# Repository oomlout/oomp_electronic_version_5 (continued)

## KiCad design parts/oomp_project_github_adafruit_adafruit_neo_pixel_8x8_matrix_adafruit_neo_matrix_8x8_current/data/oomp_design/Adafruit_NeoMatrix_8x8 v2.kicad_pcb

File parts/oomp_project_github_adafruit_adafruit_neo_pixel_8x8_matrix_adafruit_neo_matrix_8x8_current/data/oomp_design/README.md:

# OOMP KiCad design copy

Open `Adafruit_NeoMatrix_8x8 v2.kicad_pro` (or the `.kicad_pcb` / `.kicad_sch`) in KiCad. Local OOMP libraries are under `libraries/`. Original inputs are preserved in [../original/](../original/).

Only verified unchanged installed KiCad defaults were renamed. Modified, custom, unmatched and unavailable items remain unchanged. Soldering variants are never swapped during conversion. Existing pad coordinates, nets and UUIDs are preserved.

See [conversion_report.yaml](conversion_report.yaml) for every conversion and skip. Copy this directory before editing; regeneration refuses to overwrite edited design files.

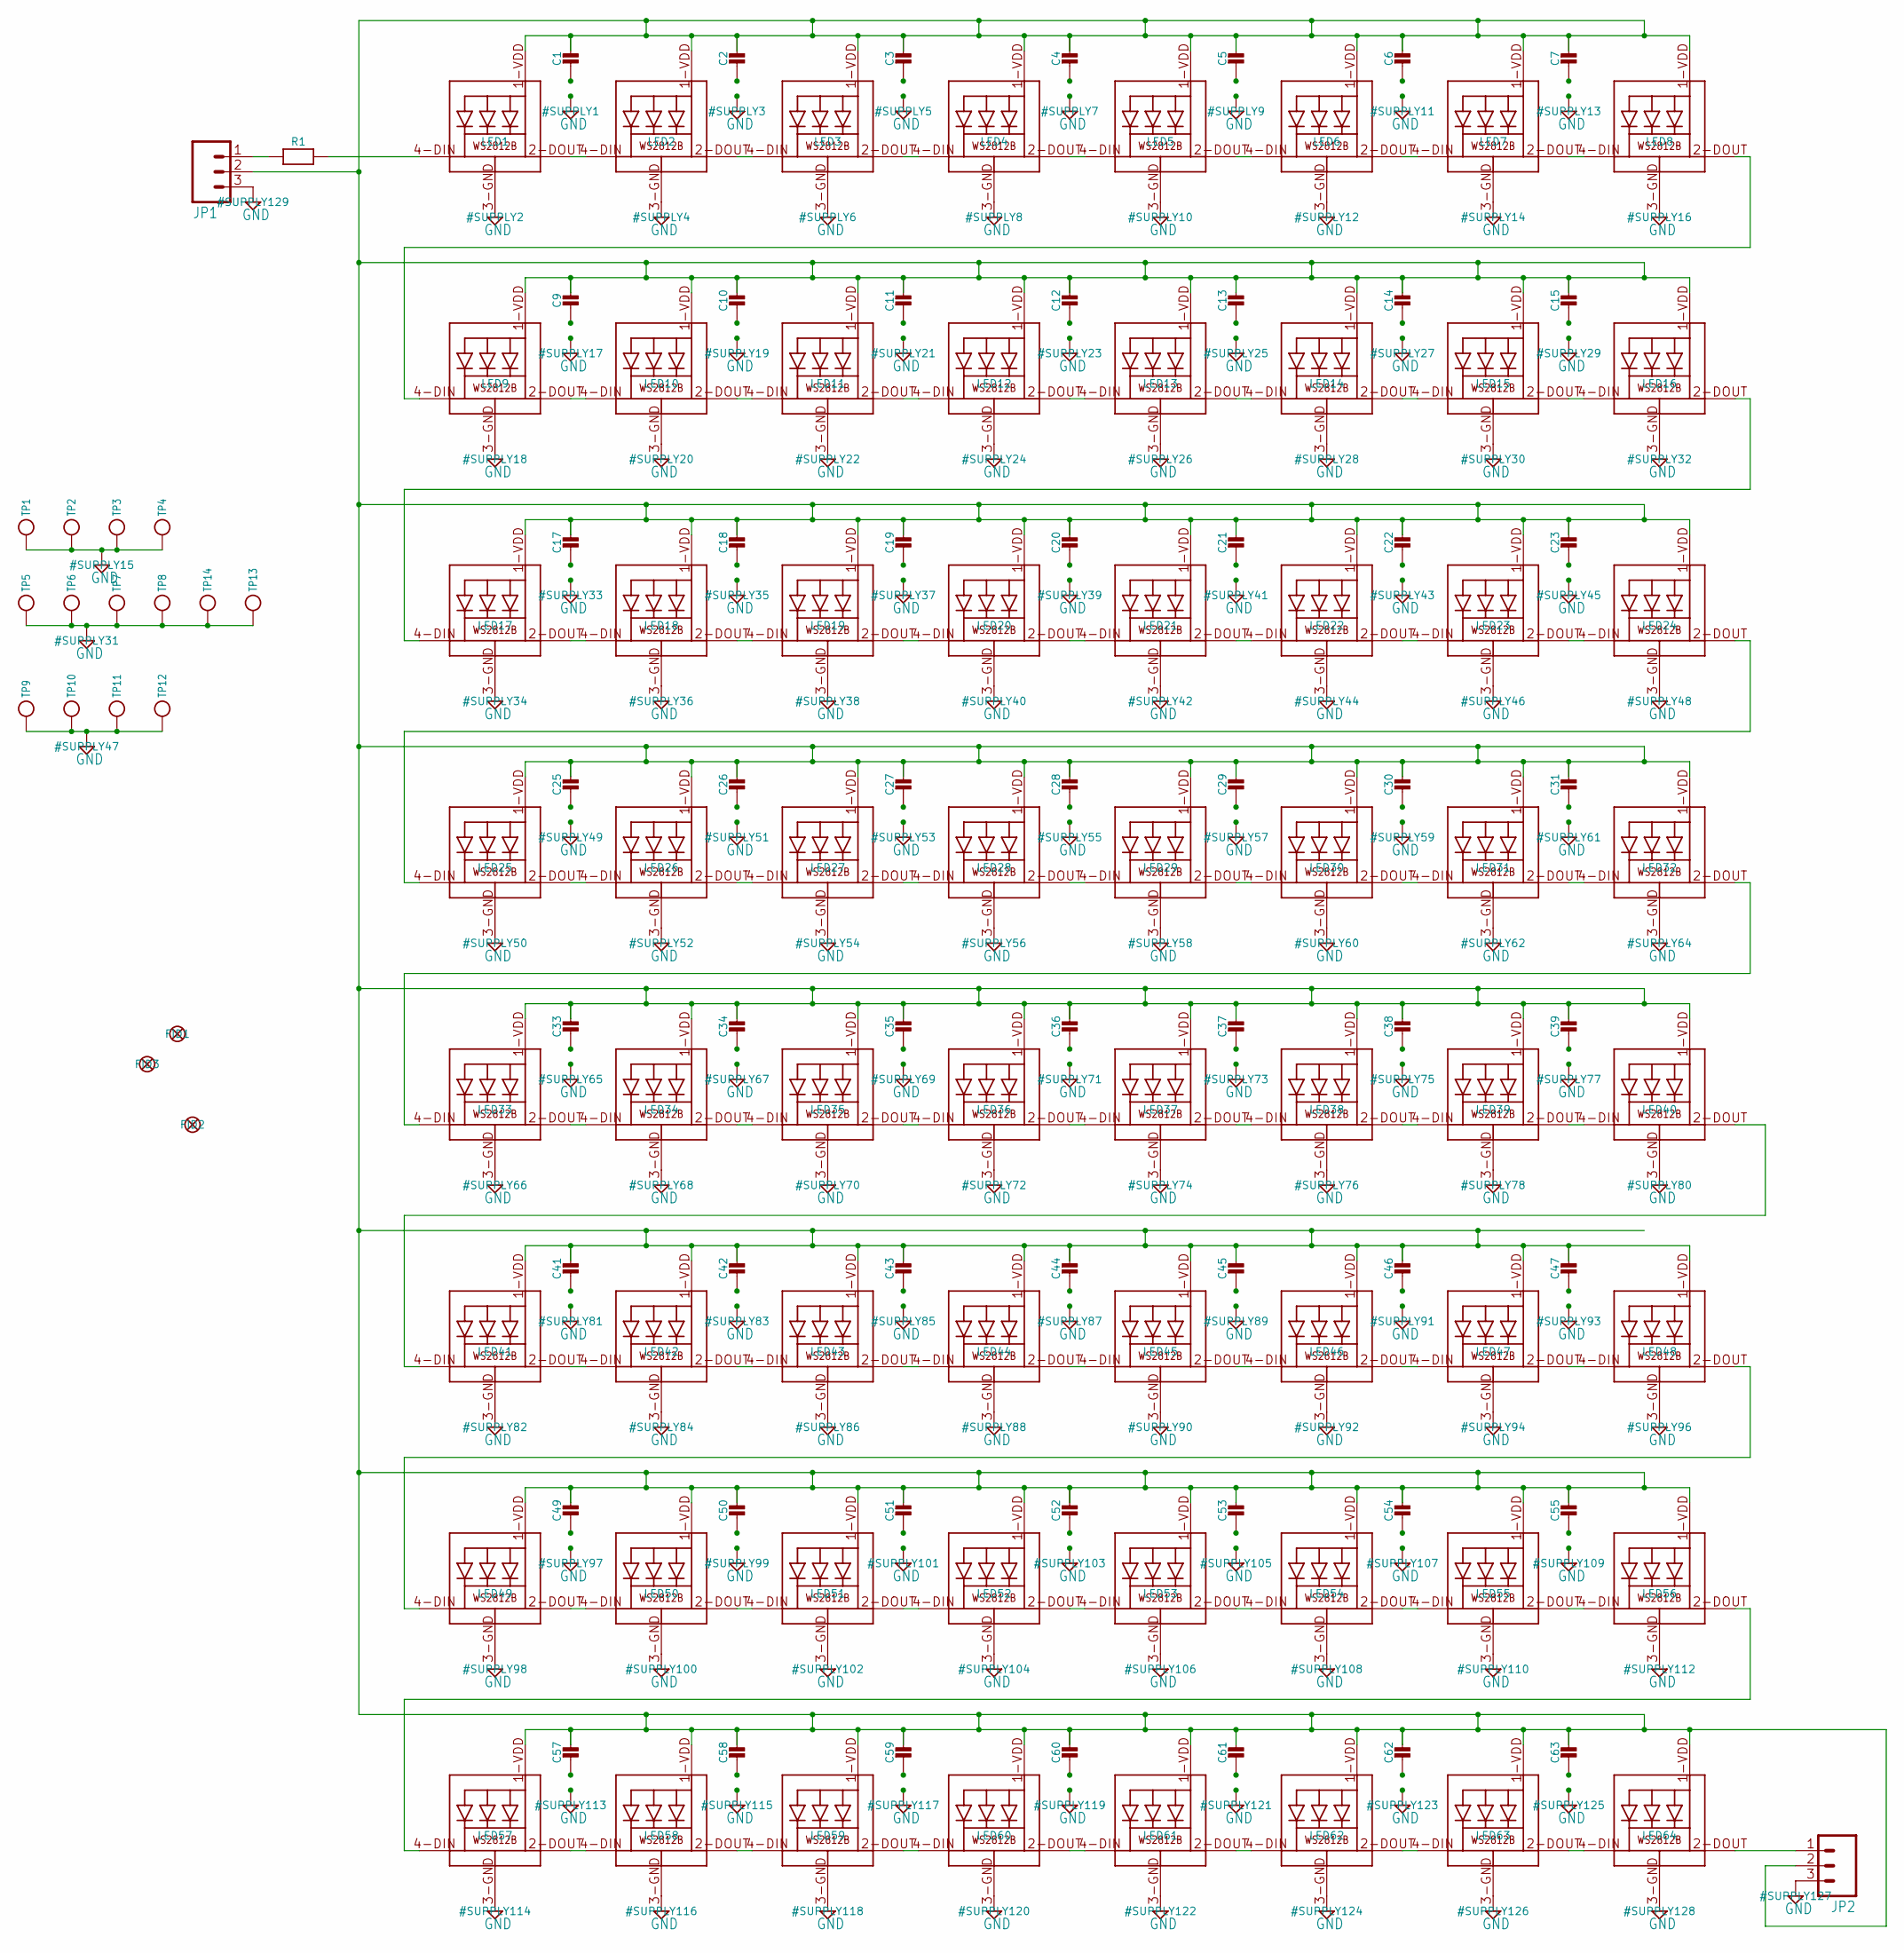
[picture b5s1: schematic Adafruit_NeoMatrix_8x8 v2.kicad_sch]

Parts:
C1, C2, C3, C4, C5, C6, C7, C9, C10, C11, C12, C13, C14, C15, C17, C18, C19, C20, C21, C22, C23, C25, C26, C27, C28, C29, C30, C31, C33, C34, C35, C36, C37, C38, C39, C41, C42, C43, C44, C45, C46, C47, C49, C50, C51, C52, C53, C54, C55, C57, C58, C59, C60, C61, C62, C63: CAP_CERAMIC0805-NOOUTLINE; 0805-NO
FID1, FID2, FID3: FIDUCIAL""; FIDUCIAL_1MM
JP1, JP2: M03PTH; 1X03
LED1, LED2, LED3, LED4, LED5, LED6, LED7, LED8, LED9, LED10, LED11, LED12, LED13, LED14, LED15, LED16, LED17, LED18, LED19, LED20, LED21, LED22, LED23, LED24, LED25, LED26, LED27, LED28, LED29, LED30, LED31, LED32, LED33, LED34, LED35, LED36, LED37, LED38, LED39, LED40, LED41, LED42, LED43, LED44, LED45, LED46, LED47, LED48, LED49, LED50, LED51, LED52, LED53, LED54, LED55, LED56, LED57, LED58, LED59, LED60, LED61, LED62, LED63, LED64: WS2812B5050; WS2812B
R1: RESISTOR0805_NOOUTLINE; 0805-NO
TP1, TP2, TP3, TP4, TP5, TP6, TP7, TP8, TP9, TP10, TP11, TP12, TP13, TP14: TESTPOINT; TESTPOINT_SMT

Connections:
GND: C1.2, C2.2, C3.2, C4.2, C5.2, C6.2, C7.2, C9.2, C10.2, C11.2, C12.2, C13.2, C14.2, C15.2, C17.2, C18.2, C19.2, C20.2, C21.2, C22.2, C23.2, C25.2, C26.2, C27.2, C28.2, C29.2, C30.2, C31.2, C33.2, C34.2, C35.2, C36.2, C37.2, C38.2, C39.2, C41.2, C42.2, C43.2, C44.2, C45.2, C46.2, C47.2, C49.2, C50.2, C51.2, C52.2, C53.2, C54.2, C55.2, C57.2, C58.2, C59.2, C60.2, C61.2, C62.2, C63.2, JP1.3, JP2.3, LED1.3-GND (GND), LED2.3-GND (GND), LED3.3-GND (GND), LED4.3-GND (GND), LED5.3-GND (GND), LED6.3-GND (GND), LED7.3-GND (GND), LED8.3-GND (GND), LED9.3-GND (GND), LED10.3-GND (GND), LED11.3-GND (GND), LED12.3-GND (GND), LED13.3-GND (GND), LED14.3-GND (GND), LED15.3-GND (GND), LED16.3-GND (GND), LED17.3-GND (GND), LED18.3-GND (GND), LED19.3-GND (GND), LED20.3-GND (GND), LED21.3-GND (GND), LED22.3-GND (GND), LED23.3-GND (GND), LED24.3-GND (GND), LED25.3-GND (GND), LED26.3-GND (GND), LED27.3-GND (GND), LED28.3-GND (GND), LED29.3-GND (GND), LED30.3-GND (GND), LED31.3-GND (GND), LED32.3-GND (GND), LED33.3-GND (GND), LED34.3-GND (GND), LED35.3-GND (GND), LED36.3-GND (GND), LED37.3-GND (GND), LED38.3-GND (GND), LED39.3-GND (GND), LED40.3-GND (GND), LED41.3-GND (GND), LED42.3-GND (GND), LED43.3-GND (GND), LED44.3-GND (GND), LED45.3-GND (GND), LED46.3-GND (GND), LED47.3-GND (GND), LED48.3-GND (GND), LED49.3-GND (GND), LED50.3-GND (GND), LED51.3-GND (GND), LED52.3-GND (GND), LED53.3-GND (GND), LED54.3-GND (GND), LED55.3-GND (GND), LED56.3-GND (GND), LED57.3-GND (GND), LED58.3-GND (GND), LED59.3-GND (GND), LED60.3-GND (GND), LED61.3-GND (GND), LED62.3-GND (GND), LED63.3-GND (GND), LED64.3-GND (GND), TP1.P$1, TP2.P$1, TP3.P$1, TP4.P$1, TP5.P$1, TP6.P$1, TP7.P$1, TP8.P$1, TP9.P$1, TP10.P$1, TP11.P$1, TP12.P$1, TP13.P$1, TP14.P$1
unnamed: LED1.4-DIN (DI), R1.2
unnamed: LED8.2-DOUT (DO), LED9.4-DIN (DI)
unnamed: LED16.2-DOUT (DO), LED17.4-DIN (DI)
unnamed: LED24.2-DOUT (DO), LED25.4-DIN (DI)
unnamed: LED40.2-DOUT (DO), LED41.4-DIN (DI)
unnamed: LED32.2-DOUT (DO), LED33.4-DIN (DI)
unnamed: LED48.2-DOUT (DO), LED49.4-DIN (DI)
unnamed: LED56.2-DOUT (DO), LED57.4-DIN (DI)
unnamed: JP2.1, LED64.2-DOUT (DO)
unnamed: JP1.1, R1.1
unnamed: LED17.2-DOUT (DO), LED18.4-DIN (DI)
unnamed: LED25.2-DOUT (DO), LED26.4-DIN (DI)
unnamed: LED26.2-DOUT (DO), LED27.4-DIN (DI)
unnamed: LED2.2-DOUT (DO), LED3.4-DIN (DI)
unnamed: LED3.2-DOUT (DO), LED4.4-DIN (DI)
unnamed: LED4.2-DOUT (DO), LED5.4-DIN (DI)
unnamed: LED5.2-DOUT (DO), LED6.4-DIN (DI)
unnamed: LED6.2-DOUT (DO), LED7.4-DIN (DI)
unnamed: LED7.2-DOUT (DO), LED8.4-DIN (DI)
unnamed: LED10.2-DOUT (DO), LED11.4-DIN (DI)
unnamed: LED11.2-DOUT (DO), LED12.4-DIN (DI)
unnamed: LED12.2-DOUT (DO), LED13.4-DIN (DI)
unnamed: LED13.2-DOUT (DO), LED14.4-DIN (DI)
unnamed: LED14.2-DOUT (DO), LED15.4-DIN (DI)
unnamed: LED15.2-DOUT (DO), LED16.4-DIN (DI)
unnamed: LED18.2-DOUT (DO), LED19.4-DIN (DI)
unnamed: LED19.2-DOUT (DO), LED20.4-DIN (DI)
unnamed: LED20.2-DOUT (DO), LED21.4-DIN (DI)
unnamed: LED21.2-DOUT (DO), LED22.4-DIN (DI)
unnamed: LED22.2-DOUT (DO), LED23.4-DIN (DI)
unnamed: LED23.2-DOUT (DO), LED24.4-DIN (DI)
unnamed: LED27.2-DOUT (DO), LED28.4-DIN (DI)
unnamed: LED28.2-DOUT (DO), LED29.4-DIN (DI)
unnamed: LED29.2-DOUT (DO), LED30.4-DIN (DI)
unnamed: LED30.2-DOUT (DO), LED31.4-DIN (DI)
unnamed: LED31.2-DOUT (DO), LED32.4-DIN (DI)
unnamed: LED1.2-DOUT (DO), LED2.4-DIN (DI)
unnamed: LED9.2-DOUT (DO), LED10.4-DIN (DI)
unnamed: LED49.2-DOUT (DO), LED50.4-DIN (DI)
unnamed: LED57.2-DOUT (DO), LED58.4-DIN (DI)
unnamed: LED58.2-DOUT (DO), LED59.4-DIN (DI)
unnamed: LED34.2-DOUT (DO), LED35.4-DIN (DI)
unnamed: LED35.2-DOUT (DO), LED36.4-DIN (DI)
unnamed: LED36.2-DOUT (DO), LED37.4-DIN (DI)
unnamed: LED37.2-DOUT (DO), LED38.4-DIN (DI)
unnamed: LED38.2-DOUT (DO), LED39.4-DIN (DI)
unnamed: LED39.2-DOUT (DO), LED40.4-DIN (DI)
unnamed: LED42.2-DOUT (DO), LED43.4-DIN (DI)
unnamed: LED43.2-DOUT (DO), LED44.4-DIN (DI)
unnamed: LED44.2-DOUT (DO), LED45.4-DIN (DI)
unnamed: LED45.2-DOUT (DO), LED46.4-DIN (DI)
unnamed: LED46.2-DOUT (DO), LED47.4-DIN (DI)
unnamed: LED47.2-DOUT (DO), LED48.4-DIN (DI)
unnamed: LED50.2-DOUT (DO), LED51.4-DIN (DI)
unnamed: LED51.2-DOUT (DO), LED52.4-DIN (DI)
unnamed: LED52.2-DOUT (DO), LED53.4-DIN (DI)
unnamed: LED53.2-DOUT (DO), LED54.4-DIN (DI)
unnamed: LED54.2-DOUT (DO), LED55.4-DIN (DI)
unnamed: LED55.2-DOUT (DO), LED56.4-DIN (DI)
unnamed: LED59.2-DOUT (DO), LED60.4-DIN (DI)
unnamed: LED60.2-DOUT (DO), LED61.4-DIN (DI)
unnamed: LED61.2-DOUT (DO), LED62.4-DIN (DI)
unnamed: LED62.2-DOUT (DO), LED63.4-DIN (DI)
unnamed: LED63.2-DOUT (DO), LED64.4-DIN (DI)
unnamed: LED33.2-DOUT (DO), LED34.4-DIN (DI)
unnamed: LED41.2-DOUT (DO), LED42.4-DIN (DI)
VDD: C1.1, C2.1, C3.1, C4.1, C5.1, C6.1, C7.1, C9.1, C10.1, C11.1, C12.1, C13.1, C14.1, C15.1, C17.1, C18.1, C19.1, C20.1, C21.1, C22.1, C23.1, C25.1, C26.1, C27.1, C28.1, C29.1, C30.1, C31.1, C33.1, C34.1, C35.1, C36.1, C37.1, C38.1, C39.1, C41.1, C42.1, C43.1, C44.1, C45.1, C46.1, C47.1, C49.1, C50.1, C51.1, C52.1, C53.1, C54.1, C55.1, C57.1, C58.1, C59.1, C60.1, C61.1, C62.1, C63.1, JP1.2, JP2.2, LED1.1-VDD (VDD), LED2.1-VDD (VDD), LED3.1-VDD (VDD), LED4.1-VDD (VDD), LED5.1-VDD (VDD), LED6.1-VDD (VDD), LED7.1-VDD (VDD), LED8.1-VDD (VDD), LED9.1-VDD (VDD), LED10.1-VDD (VDD), LED11.1-VDD (VDD), LED12.1-VDD (VDD), LED13.1-VDD (VDD), LED14.1-VDD (VDD), LED15.1-VDD (VDD), LED16.1-VDD (VDD), LED17.1-VDD (VDD), LED18.1-VDD (VDD), LED19.1-VDD (VDD), LED20.1-VDD (VDD), LED21.1-VDD (VDD), LED22.1-VDD (VDD), LED23.1-VDD (VDD), LED24.1-VDD (VDD), LED25.1-VDD (VDD), LED26.1-VDD (VDD), LED27.1-VDD (VDD), LED28.1-VDD (VDD), LED29.1-VDD (VDD), LED30.1-VDD (VDD), LED31.1-VDD (VDD), LED32.1-VDD (VDD), LED33.1-VDD (VDD), LED34.1-VDD (VDD), LED35.1-VDD (VDD), LED36.1-VDD (VDD), LED37.1-VDD (VDD), LED38.1-VDD (VDD), LED39.1-VDD (VDD), LED40.1-VDD (VDD), LED41.1-VDD (VDD), LED42.1-VDD (VDD), LED43.1-VDD (VDD), LED44.1-VDD (VDD), LED45.1-VDD (VDD), LED46.1-VDD (VDD), LED47.1-VDD (VDD), LED48.1-VDD (VDD), LED49.1-VDD (VDD), LED50.1-VDD (VDD), LED51.1-VDD (VDD), LED52.1-VDD (VDD), LED53.1-VDD (VDD), LED54.1-VDD (VDD), LED55.1-VDD (VDD), LED56.1-VDD (VDD), LED57.1-VDD (VDD), LED58.1-VDD (VDD), LED59.1-VDD (VDD), LED60.1-VDD (VDD), LED61.1-VDD (VDD), LED62.1-VDD (VDD), LED63.1-VDD (VDD), LED64.1-VDD (VDD)

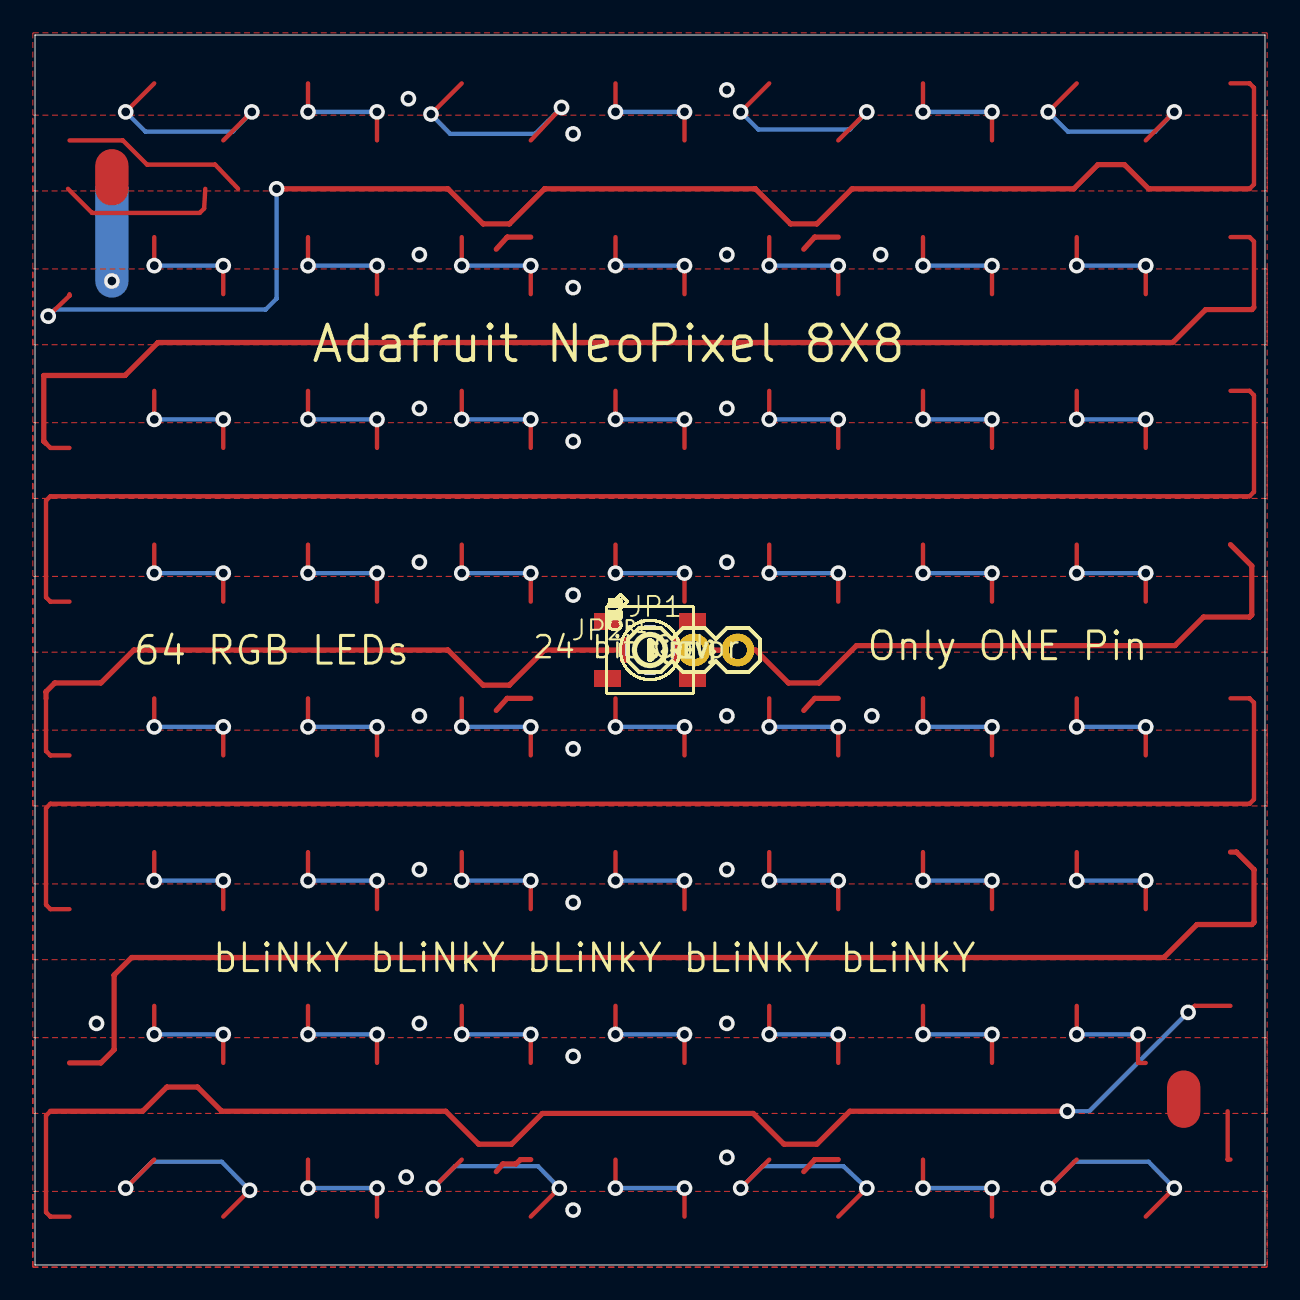
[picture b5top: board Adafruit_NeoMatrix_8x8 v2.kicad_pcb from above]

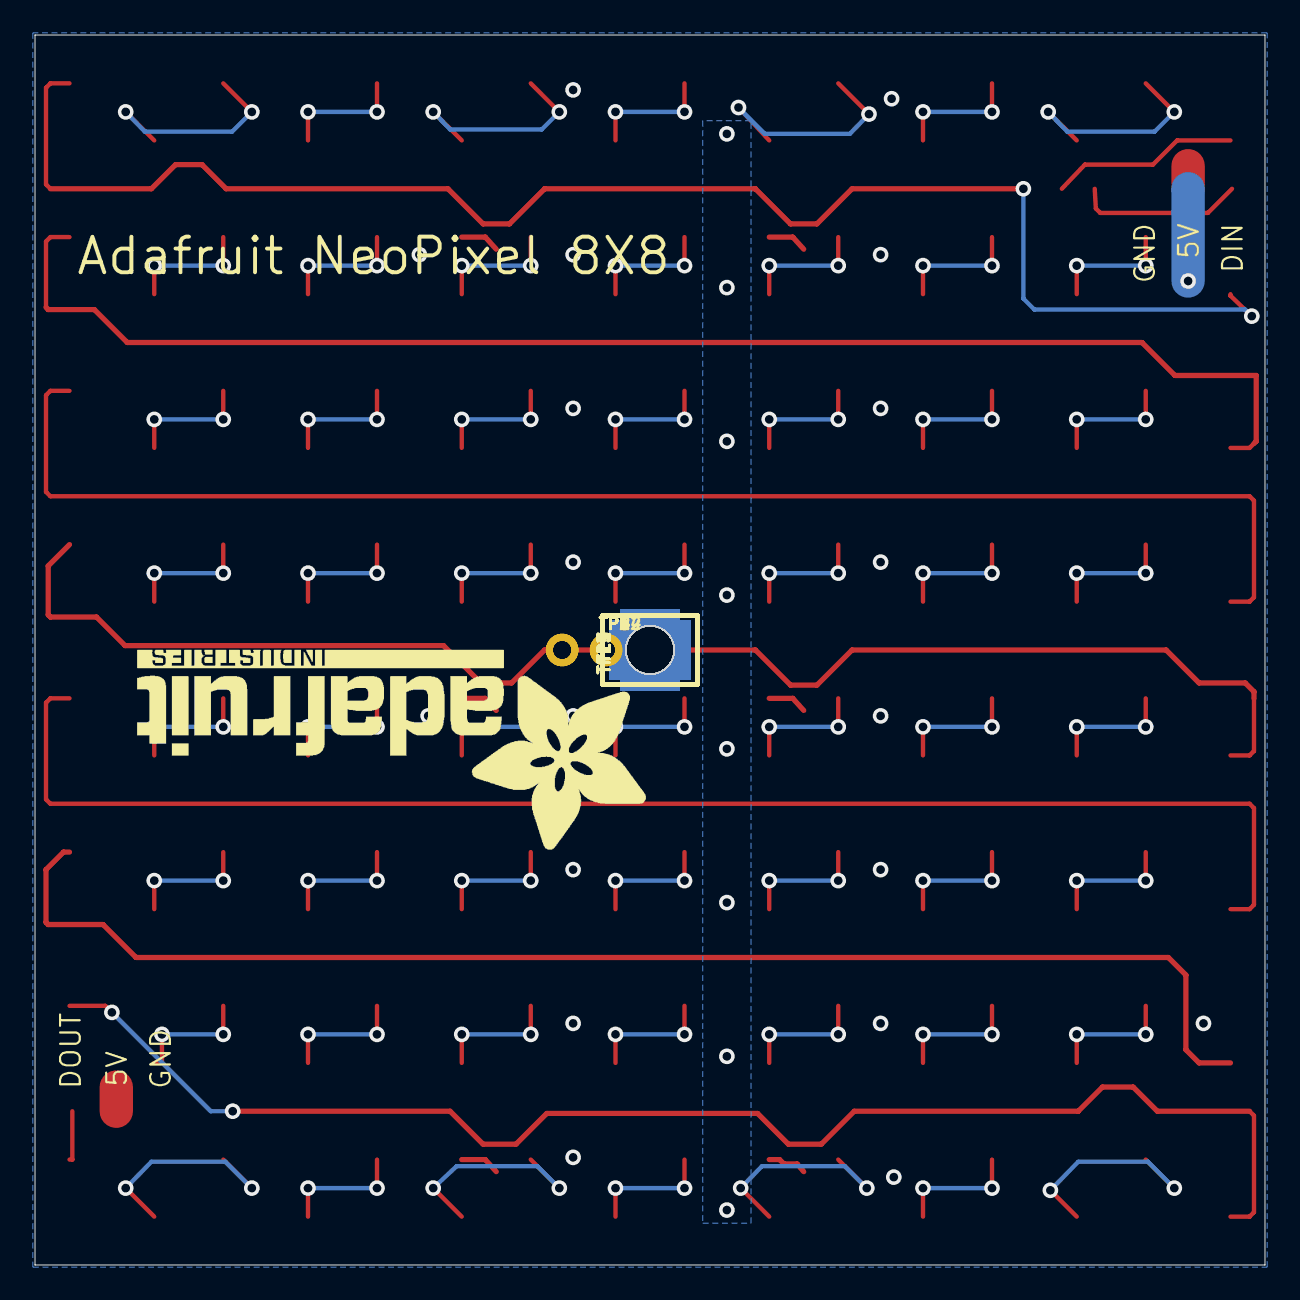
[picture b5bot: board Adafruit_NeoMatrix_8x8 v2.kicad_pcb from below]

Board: 2 copper layers, 71.1 x 71.1 mm, 154 parts (15 on the bottom side), 68 nets.

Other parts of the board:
U$1: ADAFRUIT_TEXT_30MM
U$2: PCBFEAT-REV-040
UNK_HOLE_0: dummyfp0
UNK_HOLE_1: dummyfp1
UNK_HOLE_2: dummyfp2
UNK_HOLE_3: dummyfp3
UNK_HOLE_4: dummyfp4
UNK_HOLE_5: dummyfp5
UNK_HOLE_6: dummyfp6
UNK_HOLE_7: dummyfp7
UNK_HOLE_8: dummyfp8
UNK_HOLE_9: dummyfp9
UNK_HOLE_10: dummyfp10
UNK_HOLE_11: dummyfp11

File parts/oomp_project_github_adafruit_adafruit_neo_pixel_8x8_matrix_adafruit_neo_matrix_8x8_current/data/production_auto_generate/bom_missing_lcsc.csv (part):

Designator,Comment,Footprint,OOMP ID,Reason
C1,,Adafruit_NeoMatrix_8x8 v2-import-fps:0805-NO,,No verified LCSC part number
C2,,Adafruit_NeoMatrix_8x8 v2-import-fps:0805-NO,,No verified LCSC part number
C3,,Adafruit_NeoMatrix_8x8 v2-import-fps:0805-NO,,No verified LCSC part number
C4,,Adafruit_NeoMatrix_8x8 v2-import-fps:0805-NO,,No verified LCSC part number
C5,,Adafruit_NeoMatrix_8x8 v2-import-fps:0805-NO,,No verified LCSC part number
C6,,Adafruit_NeoMatrix_8x8 v2-import-fps:0805-NO,,No verified LCSC part number
C7,,Adafruit_NeoMatrix_8x8 v2-import-fps:0805-NO,,No verified LCSC part number
C9,,Adafruit_NeoMatrix_8x8 v2-import-fps:0805-NO,,No verified LCSC part number
C10,,Adafruit_NeoMatrix_8x8 v2-import-fps:0805-NO,,No verified LCSC part number
C11,,Adafruit_NeoMatrix_8x8 v2-import-fps:0805-NO,,No verified LCSC part number
C12,,Adafruit_NeoMatrix_8x8 v2-import-fps:0805-NO,,No verified LCSC part number
C13,,Adafruit_NeoMatrix_8x8 v2-import-fps:0805-NO,,No verified LCSC part number
C14,,Adafruit_NeoMatrix_8x8 v2-import-fps:0805-NO,,No verified LCSC part number
C15,,Adafruit_NeoMatrix_8x8 v2-import-fps:0805-NO,,No verified LCSC part number
C17,,Adafruit_NeoMatrix_8x8 v2-import-fps:0805-NO,,No verified LCSC part number
C18,,Adafruit_NeoMatrix_8x8 v2-import-fps:0805-NO,,No verified LCSC part number
C19,,Adafruit_NeoMatrix_8x8 v2-import-fps:0805-NO,,No verified LCSC part number
C20,,Adafruit_NeoMatrix_8x8 v2-import-fps:0805-NO,,No verified LCSC part number
C21,,Adafruit_NeoMatrix_8x8 v2-import-fps:0805-NO,,No verified LCSC part number
C22,,Adafruit_NeoMatrix_8x8 v2-import-fps:0805-NO,,No verified LCSC part number
C23,,Adafruit_NeoMatrix_8x8 v2-import-fps:0805-NO,,No verified LCSC part number
C25,,Adafruit_NeoMatrix_8x8 v2-import-fps:0805-NO,,No verified LCSC part number
C26,,Adafruit_NeoMatrix_8x8 v2-import-fps:0805-NO,,No verified LCSC part number
C27,,Adafruit_NeoMatrix_8x8 v2-import-fps:0805-NO,,No verified LCSC part number
C28,,Adafruit_NeoMatrix_8x8 v2-import-fps:0805-NO,,No verified LCSC part number
C29,,Adafruit_NeoMatrix_8x8 v2-import-fps:0805-NO,,No verified LCSC part number
C30,,Adafruit_NeoMatrix_8x8 v2-import-fps:0805-NO,,No verified LCSC part number
C31,,Adafruit_NeoMatrix_8x8 v2-import-fps:0805-NO,,No verified LCSC part number
C33,,Adafruit_NeoMatrix_8x8 v2-import-fps:0805-NO,,No verified LCSC part number
C34,,Adafruit_NeoMatrix_8x8 v2-import-fps:0805-NO,,No verified LCSC part number
C35,,Adafruit_NeoMatrix_8x8 v2-import-fps:0805-NO,,No verified LCSC part number
C36,,Adafruit_NeoMatrix_8x8 v2-import-fps:0805-NO,,No verified LCSC part number
C37,,Adafruit_NeoMatrix_8x8 v2-import-fps:0805-NO,,No verified LCSC part number
C38,,Adafruit_NeoMatrix_8x8 v2-import-fps:0805-NO,,No verified LCSC part number
C39,,Adafruit_NeoMatrix_8x8 v2-import-fps:0805-NO,,No verified LCSC part number
C41,,Adafruit_NeoMatrix_8x8 v2-import-fps:0805-NO,,No verified LCSC part number
C42,,Adafruit_NeoMatrix_8x8 v2-import-fps:0805-NO,,No verified LCSC part number
C43,,Adafruit_NeoMatrix_8x8 v2-import-fps:0805-NO,,No verified LCSC part number
C44,,Adafruit_NeoMatrix_8x8 v2-import-fps:0805-NO,,No verified LCSC part number
C45,,Adafruit_NeoMatrix_8x8 v2-import-fps:0805-NO,,No verified LCSC part number
C46,,Adafruit_NeoMatrix_8x8 v2-import-fps:0805-NO,,No verified LCSC part number
C47,,Adafruit_NeoMatrix_8x8 v2-import-fps:0805-NO,,No verified LCSC part number
C49,,Adafruit_NeoMatrix_8x8 v2-import-fps:0805-NO,,No verified LCSC part number
C50,,Adafruit_NeoMatrix_8x8 v2-import-fps:0805-NO,,No verified LCSC part number
C51,,Adafruit_NeoMatrix_8x8 v2-import-fps:0805-NO,,No verified LCSC part number
C52,,Adafruit_NeoMatrix_8x8 v2-import-fps:0805-NO,,No verified LCSC part number
C53,,Adafruit_NeoMatrix_8x8 v2-import-fps:0805-NO,,No verified LCSC part number
C54,,Adafruit_NeoMatrix_8x8 v2-import-fps:0805-NO,,No verified LCSC part number
C55,,Adafruit_NeoMatrix_8x8 v2-import-fps:0805-NO,,No verified LCSC part number
C57,,Adafruit_NeoMatrix_8x8 v2-import-fps:0805-NO,,No verified LCSC part number
C58,,Adafruit_NeoMatrix_8x8 v2-import-fps:0805-NO,,No verified LCSC part number
C59,,Adafruit_NeoMatrix_8x8 v2-import-fps:0805-NO,,No verified LCSC part number
C60,,Adafruit_NeoMatrix_8x8 v2-import-fps:0805-NO,,No verified LCSC part number
C61,,Adafruit_NeoMatrix_8x8 v2-import-fps:0805-NO,,No verified LCSC part number
C62,,Adafruit_NeoMatrix_8x8 v2-import-fps:0805-NO,,No verified LCSC part number
C63,,Adafruit_NeoMatrix_8x8 v2-import-fps:0805-NO,,No verified LCSC part number
LED1,WS2812B5050,Adafruit_NeoMatrix_8x8 v2-import-fps:WS2812B,electronic_led_5050_rgb_ws2812b_worldsemi_ws2812b_b_w,No verified LCSC part number
LED2,WS2812B5050,Adafruit_NeoMatrix_8x8 v2-import-fps:WS2812B,electronic_led_5050_rgb_ws2812b_worldsemi_ws2812b_b_w,No verified LCSC part number
LED3,WS2812B5050,Adafruit_NeoMatrix_8x8 v2-import-fps:WS2812B,electronic_led_5050_rgb_ws2812b_worldsemi_ws2812b_b_w,No verified LCSC part number
LED4,WS2812B5050,Adafruit_NeoMatrix_8x8 v2-import-fps:WS2812B,electronic_led_5050_rgb_ws2812b_worldsemi_ws2812b_b_w,No verified LCSC part number
LED5,WS2812B5050,Adafruit_NeoMatrix_8x8 v2-import-fps:WS2812B,electronic_led_5050_rgb_ws2812b_worldsemi_ws2812b_b_w,No verified LCSC part number
LED6,WS2812B5050,Adafruit_NeoMatrix_8x8 v2-import-fps:WS2812B,electronic_led_5050_rgb_ws2812b_worldsemi_ws2812b_b_w,No verified LCSC part number
LED7,WS2812B5050,Adafruit_NeoMatrix_8x8 v2-import-fps:WS2812B,electronic_led_5050_rgb_ws2812b_worldsemi_ws2812b_b_w,No verified LCSC part number
LED8,WS2812B5050,Adafruit_NeoMatrix_8x8 v2-import-fps:WS2812B,electronic_led_5050_rgb_ws2812b_worldsemi_ws2812b_b_w,No verified LCSC part number
LED9,WS2812B5050,Adafruit_NeoMatrix_8x8 v2-import-fps:WS2812B,electronic_led_5050_rgb_ws2812b_worldsemi_ws2812b_b_w,No verified LCSC part number
LED10,WS2812B5050,Adafruit_NeoMatrix_8x8 v2-import-fps:WS2812B,electronic_led_5050_rgb_ws2812b_worldsemi_ws2812b_b_w,No verified LCSC part number
LED11,WS2812B5050,Adafruit_NeoMatrix_8x8 v2-import-fps:WS2812B,electronic_led_5050_rgb_ws2812b_worldsemi_ws2812b_b_w,No verified LCSC part number
LED12,WS2812B5050,Adafruit_NeoMatrix_8x8 v2-import-fps:WS2812B,electronic_led_5050_rgb_ws2812b_worldsemi_ws2812b_b_w,No verified LCSC part number
LED13,WS2812B5050,Adafruit_NeoMatrix_8x8 v2-import-fps:WS2812B,electronic_led_5050_rgb_ws2812b_worldsemi_ws2812b_b_w,No verified LCSC part number
LED14,WS2812B5050,Adafruit_NeoMatrix_8x8 v2-import-fps:WS2812B,electronic_led_5050_rgb_ws2812b_worldsemi_ws2812b_b_w,No verified LCSC part number
LED15,WS2812B5050,Adafruit_NeoMatrix_8x8 v2-import-fps:WS2812B,electronic_led_5050_rgb_ws2812b_worldsemi_ws2812b_b_w,No verified LCSC part number
LED16,WS2812B5050,Adafruit_NeoMatrix_8x8 v2-import-fps:WS2812B,electronic_led_5050_rgb_ws2812b_worldsemi_ws2812b_b_w,No verified LCSC part number
LED17,WS2812B5050,Adafruit_NeoMatrix_8x8 v2-import-fps:WS2812B,electronic_led_5050_rgb_ws2812b_worldsemi_ws2812b_b_w,No verified LCSC part number
LED18,WS2812B5050,Adafruit_NeoMatrix_8x8 v2-import-fps:WS2812B,electronic_led_5050_rgb_ws2812b_worldsemi_ws2812b_b_w,No verified LCSC part number
LED19,WS2812B5050,Adafruit_NeoMatrix_8x8 v2-import-fps:WS2812B,electronic_led_5050_rgb_ws2812b_worldsemi_ws2812b_b_w,No verified LCSC part number
LED20,WS2812B5050,Adafruit_NeoMatrix_8x8 v2-import-fps:WS2812B,electronic_led_5050_rgb_ws2812b_worldsemi_ws2812b_b_w,No verified LCSC part number
LED21,WS2812B5050,Adafruit_NeoMatrix_8x8 v2-import-fps:WS2812B,electronic_led_5050_rgb_ws2812b_worldsemi_ws2812b_b_w,No verified LCSC part number
LED22,WS2812B5050,Adafruit_NeoMatrix_8x8 v2-import-fps:WS2812B,electronic_led_5050_rgb_ws2812b_worldsemi_ws2812b_b_w,No verified LCSC part number
LED23,WS2812B5050,Adafruit_NeoMatrix_8x8 v2-import-fps:WS2812B,electronic_led_5050_rgb_ws2812b_worldsemi_ws2812b_b_w,No verified LCSC part number
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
